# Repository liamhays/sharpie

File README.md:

# Sharpie
Sharpie is a RP2350-based development board for Sharp color (not
monochrome!) memory-in-pixel (MiP) displays, using only the PIO
peripheral. It was originally built for the Sharp LS021B7DD02 display,
but should be compatible with any color MiP device made by Sharp. For
in-depth documentation and discussion, see the relevant blog posts [on
my website](https://cryothene.neocities.org).

Sharpie [plays](https://www.youtube.com/watch?v=W0dpXhKVE6Y)
[video](https://www.youtube.com/watch?v=7nzBJTZcFak) too!

## Repo contents
- `sharpie-cad`: a little bit of FreeCAD for a display/board carrier
- `sharpie-documents`: the LS021B7DD02 datasheet link on DigiKey is
  broken, this is the latest version from when it used to work
- `sharpie-formatter`: an image formatter written in Rust that can
  dither and format images to binary data, ready to be written
  directly to the display
- `sharpie-hw`: the original revision of the hardware, with an extra
  voltage regulator and the display connector wired backward
- `sharpie-hw-rev2`: the second revision of the hardware, with that
  extra regulator removed and the display connector wired correctly
  (this is the revision that works)
- `sharpie-pictures`: assorted pictures of the project
- `sharpie-rp2040`: initial proof-of-concept for the PIO display
  interface, running on an RP2040 instead of an RP2350.
- `sharpie-sw`: the current demo software for a Sharpie rev2 board,
  and a nearly perfect **reference implementation** for using this
  work with a display
- `sharpie-usb-display`: an actually useful demo, which streams 4:3
  video over USB to a Sharpie board
- `vdp-simulator`: some proof-of-concept Rust code for how you could
  make a Sega-inspired tile-based video display processor in software

## Licensing
The hardware in `sharpie-hw` and `sharpie-hw-rev2` is licensed under
the CERN-OHL-W. A copy of this license is in `sharpie-hw-rev2`.

All software in this repository is licensed under the GPLv3, available
in `LICENSE` in the root.

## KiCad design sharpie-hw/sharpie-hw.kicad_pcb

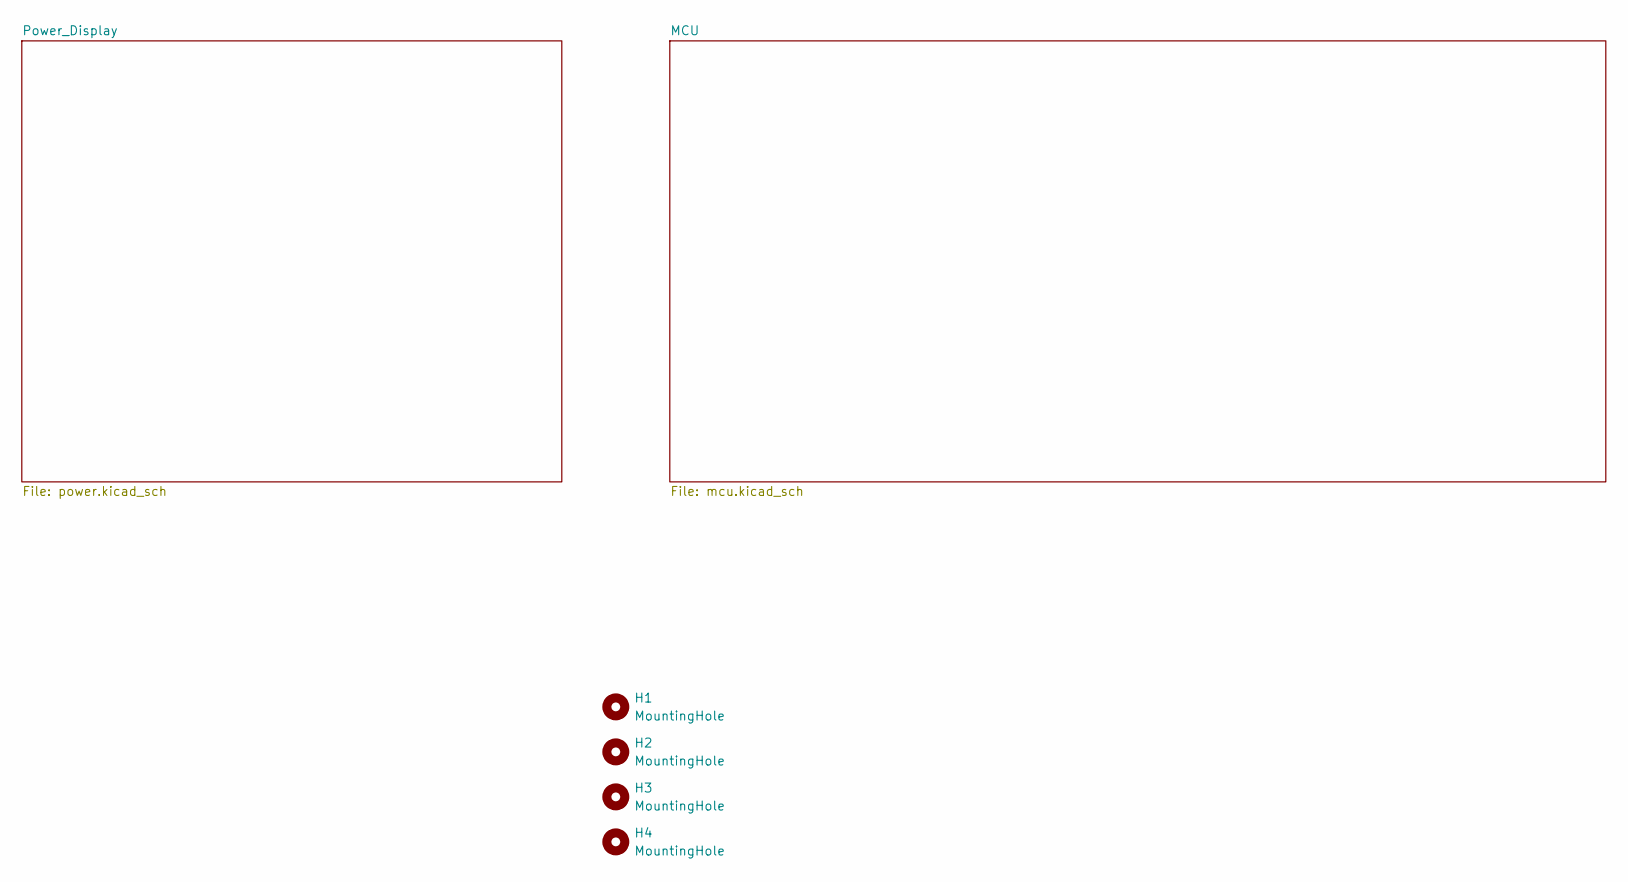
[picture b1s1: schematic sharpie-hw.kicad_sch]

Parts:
H1, H2, H3, H4: MountingHole; MountingHole_3.2mm_M3

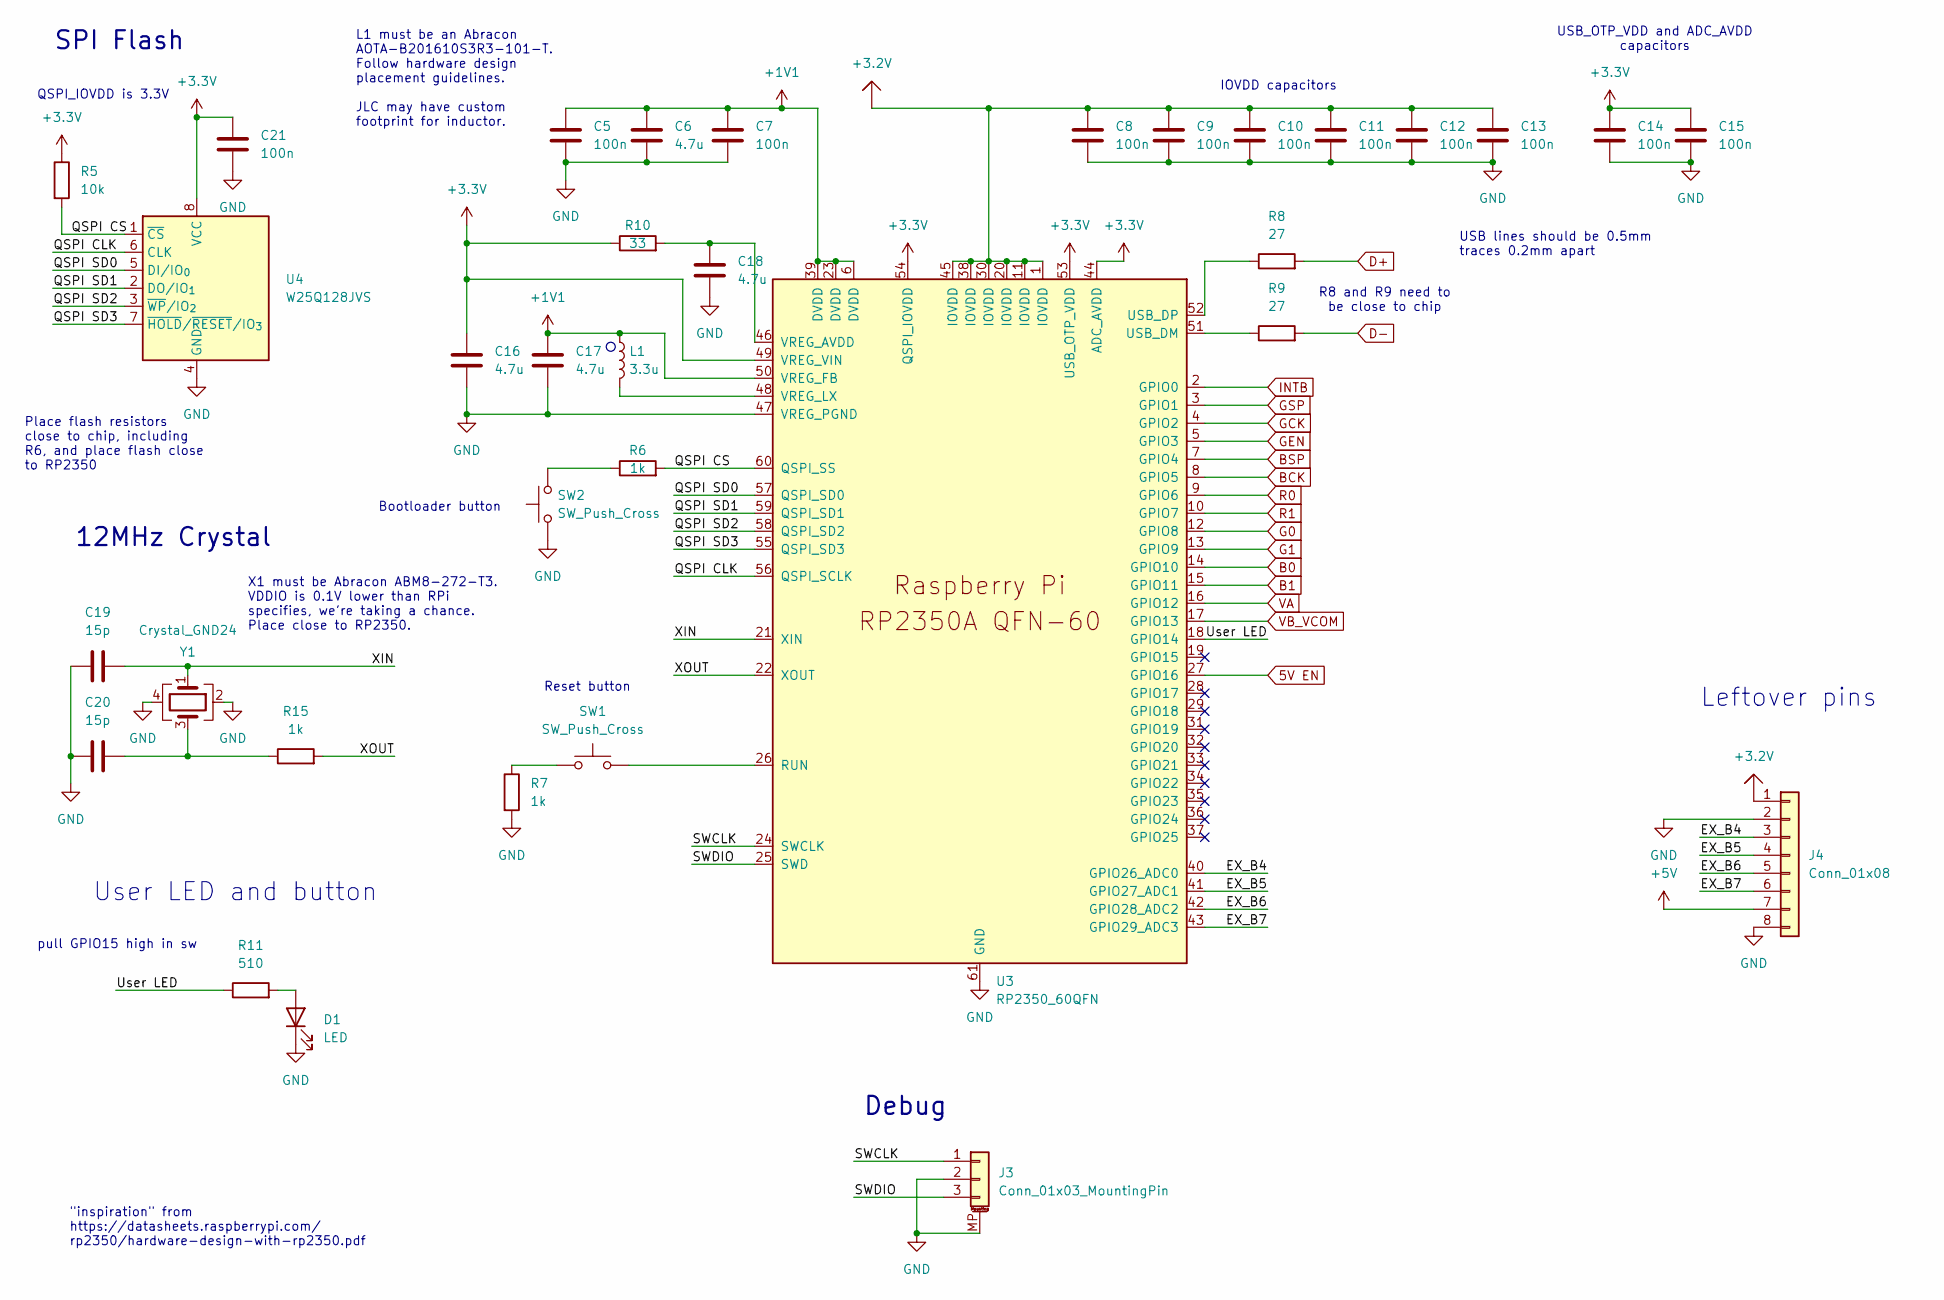
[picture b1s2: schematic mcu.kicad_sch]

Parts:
C5, C7, C8, C9, C10, C11, C12, C13, C14, C15, C21: 100n; C_0402_1005Metric; JLCPCB Part # C1525
C6, C18: 4.7u; C_0402_1005Metric; JLCPCB Part # C23733
C16, C17: 4.7u; C_0402_1005Metric_small_pads; JLCPCB Part # C23733
C19, C20: 15p; C_0402_1005Metric; JLCPCB Part # C1548
D1: LED; LED_0805_2012Metric; JLCPCB Part # C2297
J3: Conn_01x03_MountingPin; JST_SH_SM03B-SRSS-TB_1x03-1MP_P1.00mm_Horizontal; JLCPCB Part # C160403
J4: Conn_01x08; PinHeader_1x08_P2.54mm_Vertical
L1: 3.3u; L_pol_2016; JLCPCB Part # C42411119
R5: 10k; R_0402_1005Metric; JLCPCB Part # C25744
R6, R7, R15: 1k; R_0402_1005Metric; JLCPCB Part # C11702
R8, R9: 27; R_0402_1005Metric; JLCPCB Part # C25156
R10: 33; R_0402_1005Metric; JLCPCB Part # C25105
R11: 510; R_0402_1005Metric; JLCPCB Part # C25123
SW1, SW2: SW_Push_Cross; SW_PUSH_6mm
U3: RP2350_60QFN; RP2350-QFN-60-1EP_7x7_P0.4mm_EP3.4x3.4mm_ThermalVias; JLCPCB Part # C42411118
U4: W25Q128JVS; SOIC-8_5.3x5.3mm_P1.27mm; JLCPCB Part # C97521
Y1: Crystal_GND24; Crystal_SMD_3225-4Pin_3.2x2.5mm; JLCPCB Part # C20625731

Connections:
5V EN: U3.27 (GPIO16); also elsewhere on the board
+1V1: C5.1, C6.1, C7.1, C17.1, L1.1, U3.6 (DVDD), U3.23 (DVDD), U3.39 (DVDD), U3.50 (VREG_FB)
+3.2V: C8.1, C9.1, C10.1, C11.1, C12.1, C13.1, J4.1, U3.1 (IOVDD), U3.11 (IOVDD), U3.20 (IOVDD), U3.30 (IOVDD), U3.38 (IOVDD), U3.45 (IOVDD); also elsewhere on the board
+3.3V: C14.1, C15.1, C16.1, C21.1, R5.1, R10.1, U3.44 (ADC_AVDD), U3.49 (VREG_VIN), U3.53 (USB_OTP_VDD), U3.54 (QSPI_IOVDD), U4.8 (VCC); also elsewhere on the board
+5V: J4.7; also elsewhere on the board
/MCU/EX_B4: J4.3, U3.40 (GPIO26_ADC0)
/MCU/EX_B5: J4.4, U3.41 (GPIO27_ADC1)
/MCU/EX_B6: J4.5, U3.42 (GPIO28_ADC2)
/MCU/EX_B7: J4.6, U3.43 (GPIO29_ADC3)
/MCU/QSPI CLK: U3.56 (QSPI_SCLK), U4.6 (CLK)
/MCU/QSPI CS: R5.2, R6.2, U3.60 (QSPI_SS), U4.1 (~CS)
/MCU/QSPI SD0: U3.57 (QSPI_SD0), U4.5 (DI/IO_{0})
/MCU/QSPI SD1: U3.59 (QSPI_SD1), U4.2 (DO/IO_{1})
/MCU/QSPI SD2: U3.58 (QSPI_SD2), U4.3 (~WP/IO_{2})
/MCU/QSPI SD3: U3.55 (QSPI_SD3), U4.7 (~HOLD/~RESET/IO_{3})
/MCU/SWCLK: J3.1, U3.24 (SWCLK)
/MCU/SWDIO: J3.3, U3.25 (SWD)
/MCU/User LED: R11.1, U3.18 (GPIO14)
/MCU/XIN: C19.2, U3.21 (XIN), Y1.1
/MCU/XOUT: R15.2, U3.22 (XOUT)
B0: U3.14 (GPIO10); also elsewhere on the board
B1: U3.15 (GPIO11); also elsewhere on the board
BCK: U3.8 (GPIO5); also elsewhere on the board
BSP: U3.7 (GPIO4); also elsewhere on the board
D+: R8.2; also elsewhere on the board
D-: R9.2; also elsewhere on the board
G0: U3.12 (GPIO8); also elsewhere on the board
G1: U3.13 (GPIO9); also elsewhere on the board
GCK: U3.4 (GPIO2); also elsewhere on the board
GEN: U3.5 (GPIO3); also elsewhere on the board
GND: C5.2, C6.2, C7.2, C8.2, C9.2, C10.2, C11.2, C12.2, C13.2, C14.2, C15.2, C16.2, C17.2, C18.2, C19.1, C20.1, C21.2, D1.1 (K), J3.2, J3.MP (MountPin), J4.2, J4.8, R7.2, SW2.1, U3.47 (VREG_PGND), U3.61 (GND), U4.4 (GND), Y1.2, Y1.4; also elsewhere on the board
GSP: U3.3 (GPIO1); also elsewhere on the board
INTB: U3.2 (GPIO0); also elsewhere on the board
unnamed: C20.2, R15.1, Y1.3
unnamed: D1.2 (A), R11.2
unnamed: R6.1, SW2.2
unnamed: R7.1, SW1.1
unnamed: SW1.2, U3.26 (RUN)
unnamed: R9.1, U3.51 (USB_DM)
unnamed: R8.1, U3.52 (USB_DP)
unnamed: C18.1, R10.2, U3.46 (VREG_AVDD)
unnamed: L1.2, U3.48 (VREG_LX)
R0: U3.9 (GPIO6); also elsewhere on the board
R1: U3.10 (GPIO7); also elsewhere on the board
VA: U3.16 (GPIO12); also elsewhere on the board
VB_VCOM: U3.17 (GPIO13); also elsewhere on the board

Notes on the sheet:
Leftover pins
L1 must be an Abracon AOTA-B201610S3R3-101-T. Follow hardware design placement guidelines. JLC may have custom footprint for inductor.
IOVDD capacitors
Place flash resistors close to chip, including R6, and place flash close to RP2350
Reset button
User LED and button
12MHz Crystal
Bootloader button
"inspiration" from https://datasheets.raspberrypi.com/ rp2350/hardware-design-with-rp2350.pdf
pull GPIO15 high in sw
SPI Flash
USB lines should be 0.5mm traces 0.2mm apart
QSPI_IOVDD is 3.3V
Debug
USB_OTP_VDD and ADC_AVDD capacitors
X1 must be Abracon ABM8-272-T3. VDDIO is 0.1V lower than RPi specifies, we're taking a chance. Place close to RP2350.
R8 and R9 need to be close to chip

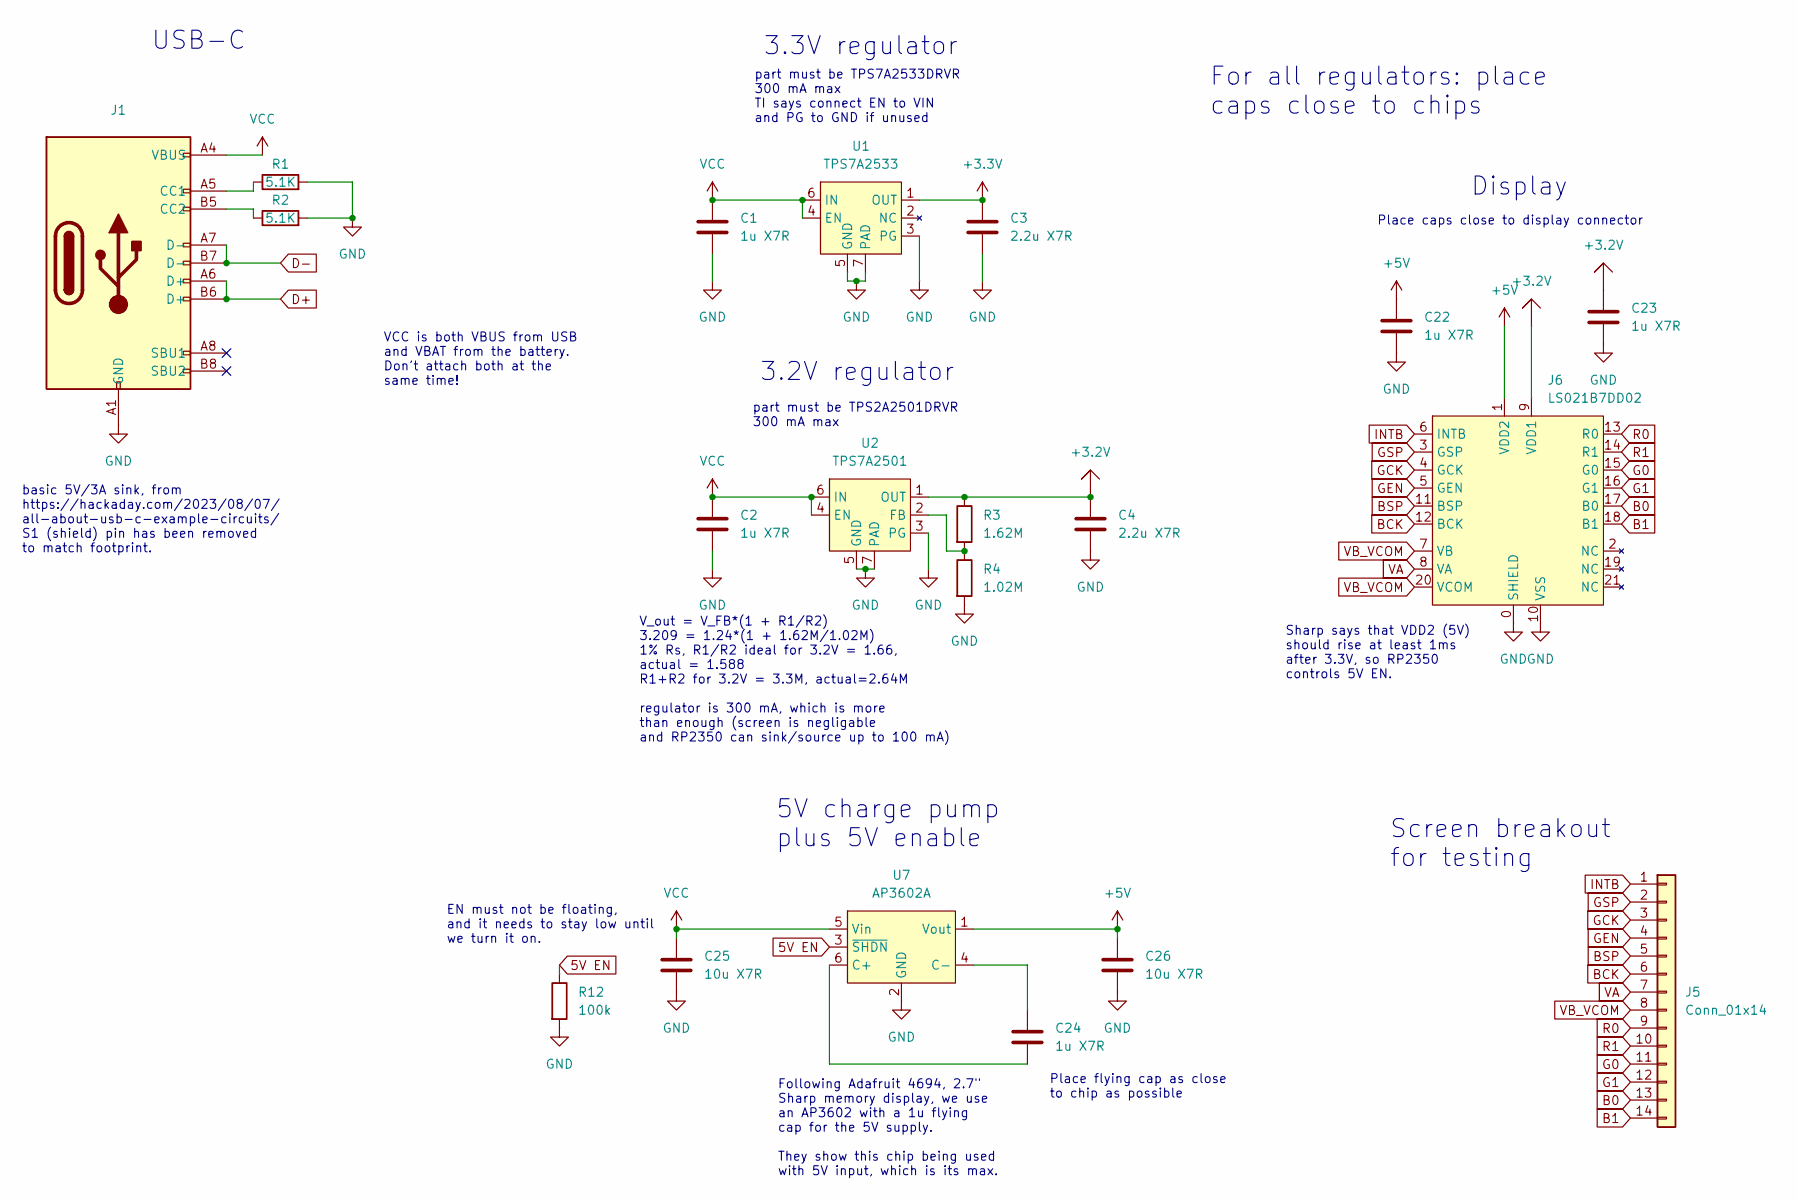
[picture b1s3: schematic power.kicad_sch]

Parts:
C1, C2, C22, C23, C24: 1u X7R; C_0805_2012Metric; JLCPCB Part # C28323
C3, C4: 2.2u X7R; C_0805_2012Metric; JLCPCB Part # C377773
C25, C26: 10u X7R; C_0805_2012Metric; JLCPCB Part # C15850
J1: TYPE-C-31-M-12; JLCPCB Part # C165948
J5: Conn_01x14; PinHeader_1x14_P2.54mm_Vertical
J6: LS021B7DD02; FPC-SMD_21P-P0.30-503566-2102
R1, R2: 5.1K; R_0402_1005Metric; JLCPCB Part # C25905
R3: 1.62M; R_0402_1005Metric; JLCPCB Part # C166525
R4: 1.02M; R_0402_1005Metric; JLCPCB Part # C26084
R12: 100k; R_0402_1005Metric; JLCPCB Part # C25741
U1: TPS7A2533; WSON-6-1EP_2x2mm_P0.65mm_EP1x1.6mm_ThermalVias; JLCPCB Part # C2867820
U2: TPS7A2501; WSON-6-1EP_2x2mm_P0.65mm_EP1x1.6mm_ThermalVias; JLCPCB Part # C2864326
U7: AP3602A; SOT-23-6; JLCPCB Part # C460358

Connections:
5V EN: R12.1, U7.3 (~SHDN); also elsewhere on the board
+3.2V: C4.1, C23.1, J6.9 (VDD1), R3.1, U2.1 (OUT); also elsewhere on the board
+3.3V: C3.1, U1.1 (OUT); also elsewhere on the board
+5V: C22.1, C26.1, J6.1 (VDD2), U7.1 (Vout); also elsewhere on the board
B0: J5.13, J6.17 (B0); also elsewhere on the board
B1: J5.14, J6.18 (B1); also elsewhere on the board
BCK: J5.6, J6.12 (BCK); also elsewhere on the board
BSP: J5.5, J6.11 (BSP); also elsewhere on the board
D+: J1.A6 (D+), J1.B6 (D+); also elsewhere on the board
D-: J1.A7 (D-), J1.B7 (D-); also elsewhere on the board
G0: J5.11, J6.15 (G0); also elsewhere on the board
G1: J5.12, J6.16 (G1); also elsewhere on the board
GCK: J5.3, J6.4 (GCK); also elsewhere on the board
GEN: J5.4, J6.5 (GEN); also elsewhere on the board
GND: C1.2, C2.2, C3.2, C4.2, C22.2, C23.2, C25.2, C26.2, J1.A1 (GND), J1.A12 (GND), J1.B1 (GND), J1.B12 (GND), J6.0 (SHIELD), J6.10 (VSS), R1.2, R2.2, R4.2, R12.2, U1.3 (PG), U1.5 (GND), U1.7 (PAD), U2.3 (PG), U2.5 (GND), U2.7 (PAD), U7.2 (GND); also elsewhere on the board
GSP: J5.2, J6.3 (GSP); also elsewhere on the board
INTB: J5.1, J6.6 (INTB); also elsewhere on the board
unnamed: J1.A5 (CC1), R1.1
unnamed: J1.B5 (CC2), R2.1
unnamed: R3.2, R4.1, U2.2 (FB)
unnamed: C24.1, U7.6 (C+)
unnamed: C24.2, U7.4 (C-)
R0: J5.9, J6.13 (R0); also elsewhere on the board
R1: J5.10, J6.14 (R1); also elsewhere on the board
VA: J5.7, J6.8 (VA); also elsewhere on the board
VB_VCOM: J5.8, J6.7 (VB), J6.20 (VCOM); also elsewhere on the board
VCC: C1.1, C2.1, C25.1, J1.A4 (VBUS), J1.A9 (VBUS), J1.B4 (VBUS), J1.B9 (VBUS), U1.4 (EN), U1.6 (IN), U2.4 (EN), U2.6 (IN), U7.5 (Vin)

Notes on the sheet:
basic 5V/3A sink, from https://hackaday.com/2023/08/07/ all-about-usb-c-example-circuits/ S1 (shield) pin has been removed to match footprint.
Place flying cap as close to chip as possible
3.3V regulator
V_out = V_FB*(1 + R1/R2) 3.209 = 1.24*(1 + 1.62M/1.02M) 1% Rs, R1/R2 ideal for 3.2V = 1.66, actual = 1.588 R1+R2 for 3.2V = 3.3M, actual=2.64M regulator is 300 mA, which is more than enough (screen is negligable and RP2350 can sink/source up to 100 mA)
EN must not be floating, and it needs to stay low until we turn it on.
3.2V regulator
Display
VCC is both VBUS from USB and VBAT from the battery. Don't attach both at the same time!
Place caps close to display connector
part must be TPS7A2533DRVR 300 mA max TI says connect EN to VIN and PG to GND if unused
For all regulators: place caps close to chips
part must be TPS2A2501DRVR 300 mA max
5V charge pump plus 5V enable
Following Adafruit 4694, 2.7" Sharp memory display, we use an AP3602 with a 1u flying cap for the 5V supply. They show this chip being used with 5V input, which is its max.
Sharp says that VDD2 (5V) should rise at least 1ms after 3.3V, so RP2350 controls 5V EN.
Screen breakout for testing
USB-C

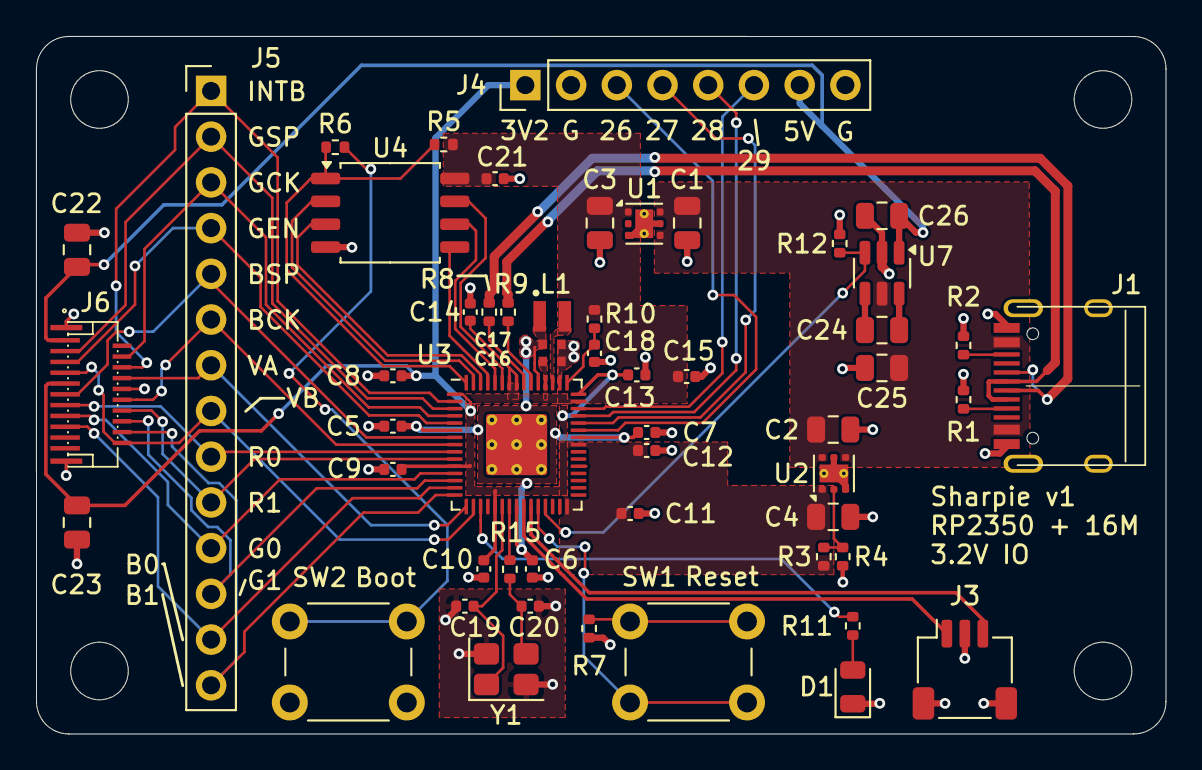
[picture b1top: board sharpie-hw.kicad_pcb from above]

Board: 2 copper layers, 62.8 x 38.8 mm, 58 parts (0 on the bottom side), 52 nets.

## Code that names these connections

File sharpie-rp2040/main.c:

#include <stdio.h>
#include <string.h>

#include "pico/stdlib.h"
#include "hardware/clocks.h"
#include "hardware/pio.h"
#include "hardware/dma.h"
#include "sharpie-vertical.pio.h"
#include "sharpie-gen.pio.h"
#include "sharpie-horiz-data.pio.h"

// Display is 320x240, one byte per pixel. A "formatted framebuffer"
// is data that can be DMAed directly to the horiz_data state machine,
// with data aligned like this:
//         MSBs of pixels                                     LSBs of pixels
// 0bB2B1G2G1R2R1    0bB4B3G4G3R4R3  (118 more)     0bB2B1G2G1R2R1    0bB4B3G4G3R4R3  (118 more)
uint8_t formatted_framebuffer[320][240];
uint32_t* formatted_framebuffer_32 = (uint32_t*)(formatted_framebuffer);

uint32_t global_32bit_zero = 0;

const int BUTTON_PIN = 16;
const int LED_PIN = 25;

void error_handler() {
  while (1) {
    gpio_put(LED_PIN, 1);
    sleep_ms(500);
    gpio_put(LED_PIN, 0);
    sleep_ms(500);
  }
}

int main() {
  stdio_init_all();

  memset(formatted_framebuffer, 0, sizeof(formatted_framebuffer));
  // init formatted framebuffer with some data that shows up nicely on the scope
  for (uint32_t i = 0; i < 320; i++) { // 10 rows is enough to start with
    for (uint32_t j = 0; j < 240; j += 2) { // whole width of row
      formatted_framebuffer[i][j] = 0xff;
      formatted_framebuffer[i][j+1] = 0xff;//0x00;
    }
  }
  // init detection button
  gpio_init(BUTTON_PIN);
  gpio_set_dir(BUTTON_PIN, false); // input
  gpio_pull_down(BUTTON_PIN);

  gpio_init(LED_PIN);
  gpio_set_dir(LED_PIN, true); // output
  
  // set system clock to 150 MHz to simulate a RP2350
  set_sys_clock_khz(150000, true);

  PIO pio = pio0;
  uint vertical_sm = 0;
  uint gen_sm = 1;
  uint horiz_data_sm = 2;
  
  uint offset = pio_add_program(pio, &sharpie_vertical_program);
  if (offset < 0) {
    printf("failed to add sharpie_vertical_program");
    error_handler();
  }
  
  // INTB on pin 0, GSP on pin 1, GCK on pin 2
  sharpie_vertical_pio_init(pio, vertical_sm, offset, 0);

  // vertical SM is running now, it will wait until we enable irq 0
  
  // the number you put on the FIFO is the number of times the loop
  // will run minus 1
  pio_sm_put(pio0, vertical_sm, 321); // run 321 times for 648 h/l total


  // init GEN state machine
  offset = pio_add_program(pio, &sharpie_gen_program);
  if (offset < 0) {
    printf("failed to add sharpie_gen_program");
    error_handler();
  }
  // GEN on pin 3, start state machine
  sharpie_gen_pio_init(pio, gen_sm, offset, 3);

  // init horiz/data state machine
  offset = pio_add_program(pio, &sharpie_horiz_data_program);
  if (offset < 0) {
    printf("failed to add sharpie_horiz_data_program");
    error_handler();
  }
  



  
  // BSP on pin 4, BCK on pin 5, data from pin 6 to 11 inclusive
  sharpie_horiz_data_pio_init(pio, horiz_data_sm, offset, 4, 6);
  
 
  // TODO: four transfers or less causes the last out data on the pins
  // to be weirdly skewed, something with just R1 and R2. Should we
  // preload the whole FIFO before starting?
  
  // Configure counters for GEN state machine and horiz-data state machine

  // GEN: run 5 times (counter value + 1)
  pio_sm_put(pio, gen_sm, 639); // this should be 639 for 640 high pulses
  pio_sm_exec(pio, gen_sm, pio_encode_pull(false, false)); // just a basic pull
  pio_sm_exec(pio, gen_sm, pio_encode_mov(pio_x, pio_osr)); // mov x, osr
  // GEN counter is now charged

  // horiz-data: charge X, make a backup in ISR (unused by any other part of the code)
  pio_sm_put(pio, horiz_data_sm, 59); // we'll get a total of 2(x+1)+4 h/l so this should be 59 => 2(59+1)+4 = 124
  pio_sm_exec(pio, horiz_data_sm, pio_encode_pull(false, false));  // pull
  pio_sm_exec(pio, horiz_data_sm, pio_encode_out(pio_isr, 32)); // out isr, 32 (make backup of counter value and clear OSR for autopull)
  pio_sm_exec(pio, horiz_data_sm, pio_encode_mov(pio_x, pio_isr)); // mov x, isr (load X with counter)
  // charge Y for total loop counter
  pio_sm_put(pio, horiz_data_sm, 640); // should be 640 for 641 loops (see 6-3-2, the last loop has data all zeros, which is why we have a chained DMA channel below)
  pio_sm_exec(pio, horiz_data_sm, pio_encode_pull(false, false)); // pull
  pio_sm_exec(pio, horiz_data_sm, pio_encode_out(pio_y, 32)); // out y, 32 (also clears OSR)


  int dma_channel = dma_claim_unused_channel(true); // true -> required
  if (dma_channel < 0) {
    printf("failed to claim dma channel\n");
    error_handler();
  }

  // DMA chaining is instantaneous, this does not affect timing.
  int dma_channel_zero = dma_claim_unused_channel(true);
  if (dma_channel_zero < 0) {
    printf("failed to claim dma zero channel\n");
    error_handler();
  }

  // configure DMA AFTER we charge the loop registers
  dma_channel_config c = dma_channel_get_default_config(dma_channel);
  channel_config_set_read_increment(&c, true); // increment reads (from the formatted framebuffer)
  channel_config_set_write_increment(&c, false); // no increment writes (into the FIFO)
  channel_config_set_transfer_data_size(&c, DMA_SIZE_32); // four byte transfers (one byte doesn't work)
  channel_config_set_dreq(&c, pio_get_dreq(pio, horiz_data_sm, true)); // true for sending data to SM
  channel_config_set_chain_to(&c, dma_channel_zero); // chain to zero channel to start zero channel when this finishes
  dma_channel_configure(dma_channel, &c,
			&pio->txf[horiz_data_sm], // destination (TX FIFO of SM 2)
			formatted_framebuffer_32, // source (formatted framebuffer)
			19200, // transfer size = 320*240/4 = 19200
			true); // start now



  dma_channel_config c_zero = dma_channel_get_default_config(dma_channel_zero);
  channel_config_set_read_increment(&c_zero, false); // just send zeros
  channel_config_set_write_increment(&c_zero, false); // write into FIFO
  channel_config_set_transfer_data_size(&c_zero, DMA_SIZE_32);
  channel_config_set_dreq(&c_zero, pio_get_dreq(pio, horiz_data_sm, true));
  dma_channel_configure(dma_channel_zero, &c_zero,
			&pio->txf[horiz_data_sm],
			&global_32bit_zero,
			240/4, // 240 bytes but 4-byte transfers
			false); // wait for chain start
  
  // all state machines have to be running in lockstep for
  // synchronization via interrupts to work
  pio_clkdiv_restart_sm_mask(pio, 0b111); // restart SM 0, 1, and 2
  while (true) {
    if (gpio_get(BUTTON_PIN)) {
      printf("setting irq\n");
      // enable irq 0 in pio 0 to start sm 0 running
      pio0->irq_force = 0b1;
      //pio0->irq_force = 0b100; // set IRQ 2
      break;
    }
  }

  while (true);
}

    

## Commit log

2025-01-12 Initial commit of sharpie-formatter
2025-01-12 Initial commit of sharpie-rp2040.
2025-01-12 sharpie-formatter: LUT generation: use shifting and OR, not adds, for the index computation
2025-01-12 Add initial hardware design, probably not complete but close.
2025-01-19 sharpie-hw prototype 1: complete
2025-01-29 Finalize schematic, start PCB, configure manufacturing parameters, and start placing RP2350 components.
2025-02-07 Modify FPC footprint, add alternate USB-C footprint, and commit final (before review) design.
2025-02-12 Add all JLCPCB part numbers and some PCB silkscreens.
2025-02-19 Fix some BOM entries and routing choices.
2025-02-19 Adjust display regulators to match datasheet, so they're now 1u 0805.
2025-02-23 Adjust orientation of necessary parts for JLCPCB assembly.
2025-02-26 Move to as many JLCPCB basic parts as possible and remove user button.
2025-02-28 Fix two items: battery connector polarity and AP3602 capacitor polarity.
2025-06-08 Add vdp_simulator with one tilemap layer rendering, including scroll.
2025-09-11 PCB changes of some kind: appears to be the version sent to JLC.
    The manufactured version of the PCB has no voltage divider or battery input,
    because they were unnecssary (and in the case of the battery input,
    unsafe).
2025-09-11 Add UnformatRaw to sharpie-formatter.
2025-09-24 Add sharpie-cad including sharpie-carrier.FCStd for putting the whole thing on.
2025-09-28 Add sharpie-sw, currently configured to use 3 PIO blocks (untested).
    Using and reusing one PIO and two DMAs makes it...not work, in ways
    I can't figure out. Using 3 PIOs and 6 DMAs might make it work.
2025-09-28 Add sharpie-cad, including super basic board+screen carrier.
2025-09-29 sharpie-sw generates proper waveforms, but the display still doesn't work.
    The issue was that the zeros DMA stream was configured to send twice
    as much data as it's supposed to, so it never finished, and everything
    afterward got messed up.
2025-10-02 Add sharpie-hw-rev2. The version in this commit is the one sent to production.
2025-10-21 Sharpie works! This commit is mostly to mark functional code.
2025-10-27 Add Floyd-Steinberg dithering to sharpie-formatter.
2025-10-28 Refactor some parts and add DitherFormat command to dither image and format to screen fromat.
2025-10-28 Update image to 0.25.8 and set color transfer function to linearize image colors.
2025-10-28 Fully convert image to sRGB linear and clean up some other code.
2025-12-19 Add partial update code, which makes correct waveforms but doesn't quite work.
    Main sharpie-sw code also stopped working after adding the partial code, even
    when it doesn't run.
2025-12-19 Fix partial update SM pin configuration and partial update works!
2025-12-22 Make INTB fall after irq set from GCK end SM instead of on a timer.
2025-12-24 Clean up partial-gck.pio and add pencils.jpg.
2025-12-24 Add sharpie-handheld.jpg.
2025-12-24 Add README.md.
2025-12-24 Change image in README.md to be smaller.
2025-12-24 Fix link in README.md too.
2025-12-24 Finalize README.md: image and grammar
2025-12-24 Fix partial updates that begin at the top of the frame.
    These start at GCK2, like in a full update, so the GCK SM has to
    be able to take GCK2 into the main loop.
2025-12-31 Add sharpie-documents and the LS021 datasheet.
2025-12-31 Move VA/VB/VCOM to just PWM, no CPU involvement.
    Also delete sharpie-va-vb-vcom.pio, which was way overkill for VA/VB/VCOM.
2026-01-02 Correct GCK changed lows to fix overall timing.
    Also add note about initial changed section counter not needing the -1
    that the rest of them do.
2026-01-04 Major refactor of main.c and fix extra GEN if partial frame starts with changes.
2026-02-01 Remove gen-luts and add dither-dir, rotate-dir, and full-format-dir to sharpie-formatter.
2026-02-02 Add common/ with CMake and PIO files and softlink sharpie-sw resources to them.
2026-02-02 Add pencils.jpg and its generated output, pencils.h, to sharpie-sw.
    (This is a good test image).
2026-02-02 Add sharpie-usb-display/ and sharpie-formatter/the_gang.
2026-02-02 Add .gitignore in hw-rev2 and remove extra file in sharpie-usb-display.
2026-02-04 Add clap to sharpie-usb-display and update some READMEs.
2026-02-12 Test differential dithering and add note about Matroska video.
2026-02-12 Add videos to README and 3D rendering of PCB to sharpie-hw-rev2.
2026-02-12 Add CERN-OHL-W and GPLv3 licenses and add licenses note.
2026-02-13 Add sharpie-documents description.
2026-02-21 Move back to launch() because it works.
